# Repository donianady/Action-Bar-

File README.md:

# Action Bar

A simple macropad consists of 5 switches, a rotatry encoder, rp2040, custom pcb and case.

## Dimensions

PCB dimensions: 65.0mm * 84.5mm.
Case Dimension: 81.4mm * 90.0mm.

## BOM

- 5 cherry MX Key Switches
- 1x Rotary Encoder With Switch
- Seeduino XIAO RP2040
- 3D printing
-PCB Manifacture

## Features
- **Compact & Ergonomic:** 5 mechanical switches paired with a multi-functional rotary encoder.
- **Powered by RP2040:** Built using the Seeeduino XIAO RP2040 for reliable performance and easy programmability via QMK/VIAL/CircuitPython.
- **Custom Design:** Features a custom-designed PCB and a 3D-printed enclosure.

## Assembly Instructions
1. **PCB & Soldering:** Solder the Seeeduino XIAO RP2040, switches, and rotary encoder onto the custom PCB.
2. **Enclosure:** Mount the assembled electronics into the 3D-printed case.
3. **Flashing:** Connect via USB-C and flash the firmware.

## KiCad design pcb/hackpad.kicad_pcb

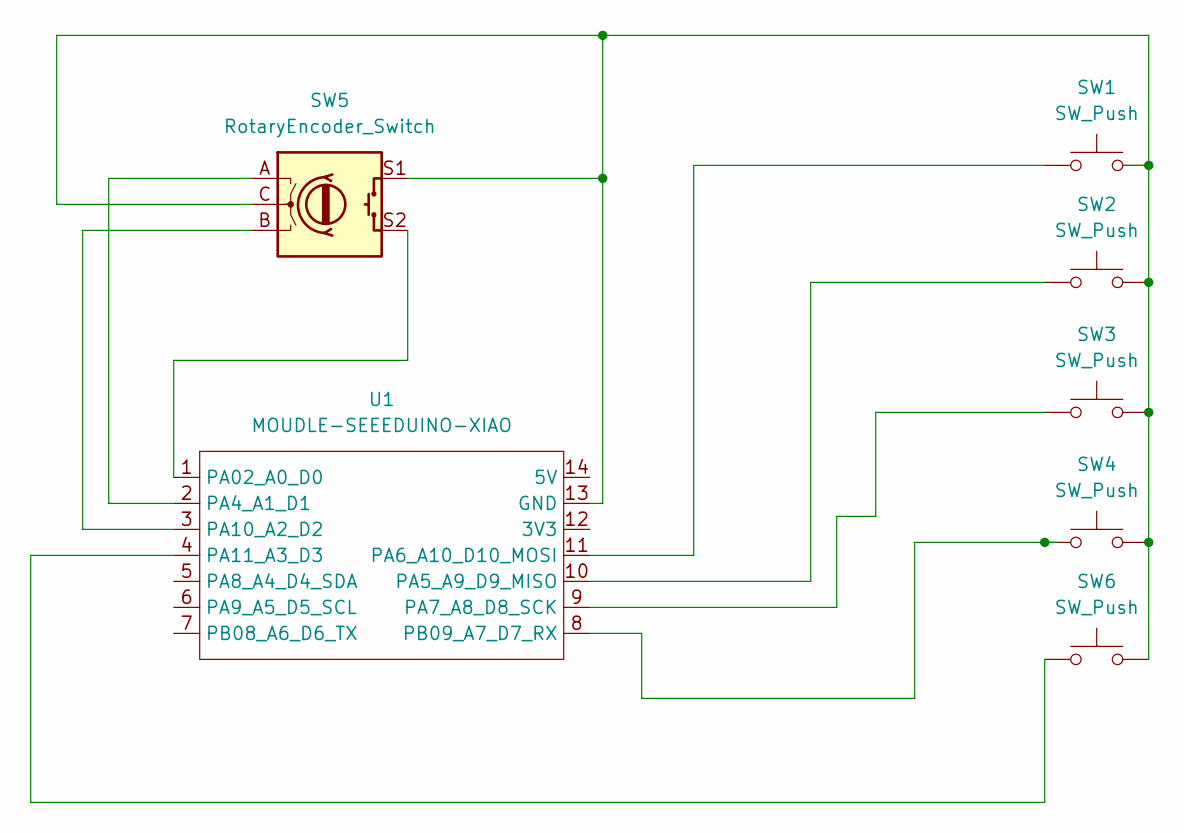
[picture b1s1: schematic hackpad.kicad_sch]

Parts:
SW1, SW2, SW3, SW4, SW6: SW_Push; SW_Cherry_MX_1.00u_PCB
SW5: RotaryEncoder_Switch; RotaryEncoder_Alps_EC11E-Switch_Vertical_H20mm_CircularMoun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
U1: MOUDLE-SEEEDUINO-XIAO; XIAO-Generic-Hybrid-14P-2.54-21X17.8MM

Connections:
unnamed: SW1.2, SW2.2, SW3.2, SW4.2, SW5.C, SW5.S1, SW6.2, U1.13 (GND)
unnamed: SW5.S2, U1.1 (PA02_A0_D0)
unnamed: SW5.A, U1.2 (PA4_A1_D1)
unnamed: SW2.1, U1.10 (PA5_A9_D9_MISO)
unnamed: SW1.1, U1.11 (PA6_A10_D10_MOSI)
unnamed: SW3.1, U1.9 (PA7_A8_D8_SCK)
unnamed: SW5.B, U1.3 (PA10_A2_D2)
unnamed: SW6.1, U1.4 (PA11_A3_D3)
unnamed: SW4.1, U1.8 (PB09_A7_D7_RX)

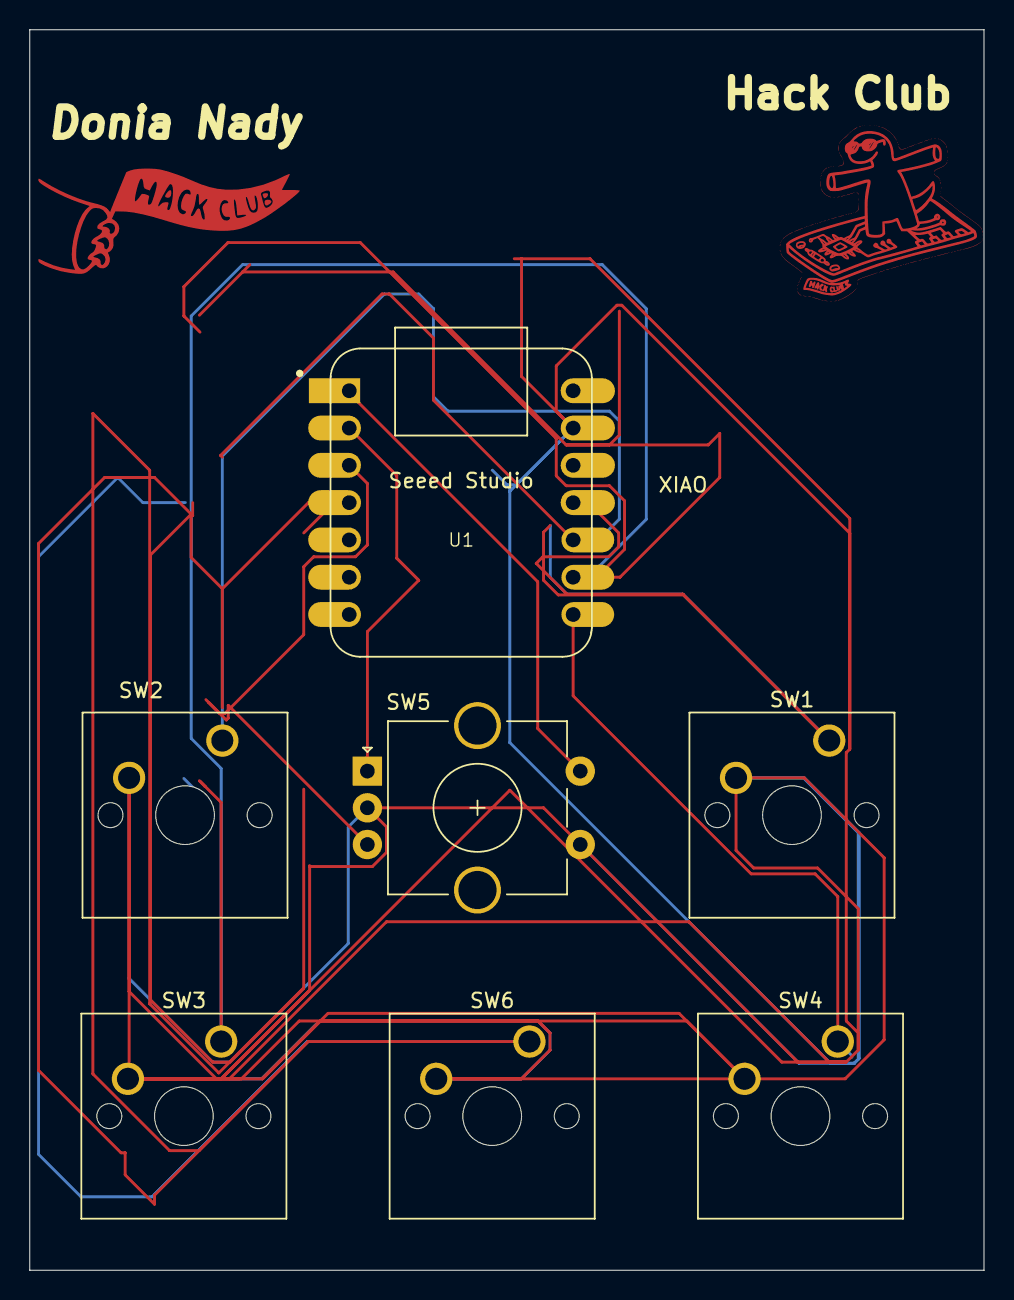
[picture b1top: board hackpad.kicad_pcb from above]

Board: 2 copper layers, 65.0 x 84.5 mm, 7 parts (0 on the bottom side), 9 nets.
